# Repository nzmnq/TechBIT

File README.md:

# TechBIT — B2B IoT-система діагностики коліс, гальм та підшипників (v2.0/v2.2)

Єдиний монорепозиторій проєкту **TechBIT** на гілці `main`: багаторольова прошивка **ESP32-C3 / ESP32-S3** (CAN + ESP-NOW + Rule Engine + Black Box + LTE + BLE), апаратна плата **KiCad 10**, інженерний **React SPA** діагностичний стенд та комерційна **B2B IoT + SaaS** веб-платформа.

---

## Структура монорепозиторію

| Модуль | Призначення | Документація |
|---|---|---|
| [`website/`](website/) | B2B IoT + SaaS платформа, калькулятор ROI автопарку, Drop & Hook моніторинг, `AdminPage`, i18n (`uk`/`en`), React + Express API | [website/README.md](website/README.md) |
| [`hardware/`](hardware/) | Принципові схеми та розводка плат у `KiCad 10` (`Wheel_Sensor_Amplifier` для коліс і `S3_Master_Hub` для кабіни), 3D-моделі (`.wrl`), рендери, PDF 1:1 для ЛУТ/УФ-маски та Python-генератори | [hardware/README.md](hardware/README.md) |
| [`firmware/`](firmware/) | Прошивка `PlatformIO` TechBIT v2.0 (`c3_node`, `c3_trailer_bridge` ESP-NOW, `s3_master` Black Box + LTE + BLE, нативні тести `native_test`) | [firmware/README.md](firmware/README.md) |
| [`workbench/`](workbench/) | Інженерний стенд TechBIT v2.2 (`React Router` + `Vite` SPA + `Node.js` + `Web Serial` / Wi-Fi POST + `SSE`, порт `5050`) | [workbench/README.md](workbench/README.md) |
| [`.plans/`](.plans/) | Архітектурна специфікація об'єднання гілок у монорепозиторій | [monorepo-unification-spec.md](.plans/monorepo-unification-spec.md) |

---

## Швидкий старт за модулями

Кожен модуль є самодостатнім і запускається зі своєї підпапки:

### 1. B2B Веб-платформа ([`website/`](website/))
```bash
cd website
npm run install:all   # одноразове встановлення залежностей server/ та client/
npm run build         # збірка клієнта у website/client/dist/
npm run server        # Node.js API + роздача клієнта на http://localhost:5000
npm run client        # React dev-сервер на http://localhost:5173
```

### 2. Прошивка v2.0 ([`firmware/`](firmware/))
Відкрийте папку `firmware/` у VS Code (PlatformIO) або використовуйте CLI `pio`:
```bash
cd firmware
pio run -e c3_node            # уніфікований осьовий вузол (ESP32-C3)
pio run -e c3_trailer_bridge  # бездротовий шлюз причепа CAN -> ESP-NOW (ESP32-C3)
pio run -e s3_master          # головний блок у кабіні (ESP32-S3)
pio test -e native_test       # нативні юніт-тести DSP, CAN v2, Rules та BlackBox
```

### 3. Діагностичний SPA-стенд ([`workbench/`](workbench/))
```bash
cd workbench
npm ci                # або npm install
npm run build         # збірка SPA у workbench/dist/
npm test              # юніт- та інтеграційні тести (test_truthfulness.js)
npm start             # запуск веб-стенду на http://localhost:5050 (Chrome/Edge для Web Serial)
```

### 4. Апаратна частина та PCB ([`hardware/`](hardware/))
- Відкрийте [`hardware/kicad/Wheel_Sensor_Amplifier.kicad_pro`](hardware/kicad/Wheel_Sensor_Amplifier.kicad_pro) у **KiCad 10** (3D-моделі підключаються через відносні шляхи `${KIPRJMOD}/../3dmodels/`).
- Готові PDF 1:1 для ЛУТ, УФ-маски та монтажу розміщено у [`hardware/print/`](hardware/print/).

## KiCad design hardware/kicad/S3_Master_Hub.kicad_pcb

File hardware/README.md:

# TechBIT Hardware — Апаратна частина (колісний вузол + головний блок `ESP32-S3`)

Апаратна частина системи моніторингу вібрації, стану гальм/підшипників та температури коліс автомобіля **TechBIT** (**KiCad 10 PCB**, **3D-моделі `.wrl`**, **генератори** та **PDF 1:1 для ЛУТ і УФ-маски**).  
Нижче описані обидві плати системи:
1. **Плата колісного вузла (`Wheel_Sensor_Amplifier`, `66 × 50 мм`)** — `ESP32-C3 SuperMini` + зарядовий підсилювач `MCP6002` + `GY-SHT40` + `CAN`.
2. **Плата головного блоку в кабіні (`S3_Master_Hub`, `71 × 96 мм`)** — `ESP32-S3-DevKitC-1 N16R8` + `CAN (SN65HVD230 + 120 Ω)` + круглий `1.28" GC9A01 SPI TFT` + `microSD`.

---

## 1. Плата колісного вузла (`Wheel_Sensor_Amplifier`)

| Вигляд зверху (`F.Cu` — модулі та THT) | Вигляд знизу (`B.Cu` — SMD на міді) |
|---|---|
|  |  |

---

## Структура папки `hardware/`

```text
hardware/
├── kicad/                                      # Проєкти KiCad 10
│   ├── Wheel_Sensor_Amplifier.kicad_pro        # Проєкт колісного вузла
│   ├── Wheel_Sensor_Amplifier.kicad_sch        # Принципова схема колісного вузла
│   ├── Wheel_Sensor_Amplifier.kicad_pcb        # Розводка (66 × 50 мм, 1 шар B.Cu)
│   ├── Wheel_Sensor_Amplifier_Panel_A4.kicad_pcb  # Панель 3×5 (15 плат на аркуш A4)
│   ├── S3_Master_Hub.kicad_pro                 # Проєкт головного блоку ESP32-S3
│   ├── S3_Master_Hub.kicad_sch                 # Принципова схема та розпіновка S3 Master
│   ├── S3_Master_Hub.kicad_pcb                 # Розводка (71 × 96 мм, 1 шар B.Cu)
│   └── S3_Master_Hub_Panel_A4.kicad_pcb        # Панель 2×3 (6 плат на аркуш A4)
├── 3dmodels/                                   # Локальні 3D-моделі модулів (.wrl)
├── renders/                                    # 3D-рендери та читабельні схеми розмітки (.png)
├── print/                                      # Готові PDF 1:1 для ЛУТ, УФ-маски та монтажу
├── scripts/                                    # Python-скрипти генерації проєктів і макетів
│   ├── generate_project.py                     # Генератор колісного вузла (single + 15x panel)
│   ├── make_plate_151x102.py                   # Аркуші під текстоліт 151×102 мм (колісний вузол)
│   ├── make_a4_mixed_sheet.py                  # Змішаний аркуш A4 (5 комплектів колісного вузла)
│   ├── make_top_half_stencils.py               # УФ-маска на верхню половину A4 (колісний вузол)
│   ├── generate_s3_master.py                   # Генератор головного блоку S3_Master_Hub (single + 6x panel)
│   └── make_s3_master_prints.py                # Генератор PDF 1:1, інструкції та 3D-рендерів S3_Master_Hub
└── README.md
```

---

## Технічні характеристики плати (`Wheel Sensor Amplifier`)

- **Габарити однієї плати:** `66.0 × 50.0 мм` (оптимально для розміщення `2×2 = 4` плат на заготовці `151×102 мм` або `3×5 = 15` плат на A4).
- **Топологія:** **одностороння мідь (`B.Cu`)**, розведена без перемичок та без масивної заливки `GND` — розрахована під домашнє травлення (ЛУТ + лимонна кислота / перекис водню або хлорне залізо).
- **Гідроізоляція під заливку компаундом:** усі силові, шинні та сенсорні інтерфейси (`J1`, `J2`, `J3`) винесені кутовими роз'ємами по периметру для зручного заливання плати епоксидною смолою.
- **Паяльна маска:** розширення вікон `pad_to_mask_clearance = 0.15 мм`, суцільне заповнення контактних площадок на фотошаблонах (`B.Mask`).

---

## Склад компонентів (BOM)

### Верхня сторона (`F.Cu` — вивідні компоненти, модулі та роз'єми)
| Позиція | Компонент / Модуль | Номінал / Тип | Призначення |
|---|---|---|---|
| `U2` | Мікроконтролер | `ESP32-C3 SuperMini` | Оцифровка АЦП, I2C, CAN/TWAI (`USB-C` донизу) |
| `U1` | Операційний підсилювач | `MCP6002-I/P` (панелька `DIP-8`) | Зарядовий підсилювач ($K \approx 3$) + буфер |
| `MOD1` | DC-DC понижувач | `Mini360` (`12V → 5V`) | Живлення вузла від бортмережі авто |
| `MOD2` | CAN-трансивер | `SN65HVD230` (3.3V, 6-pin) | Інтерфейс CAN-шини (`CANH` / `CANL`) |
| `J1` | Клемник датчика вібрації | `15EDGR-5.08-02P` / `KF301-2P` (кутовий) | Вхід п'єзодатчика (`1=PIEZO+`, `2=GND`) |
| `J2` | Клемник живлення та CAN | `15EDGR-5.08-04P` / `KF301-4P` (кутовий) | Автомагістраль (`1=+12V`, `2=GND`, `3=CAN_L`, `4=CAN_H`) |
| `J3` | Роз'єм датчика температури | `JST-XH S4B-XH-A` (4-pin, кутовий 2.5 мм) | Вологостійкий датчик `GY-SHT40` (`1=3V3`, `2=GND`, `3=SDA`, `4=SCL`) |
| `R1` | Резистор THT 0.25W | `10 kΩ` | Обмеження вхідного струму ОП |
| `R2`, `R3` | Резистори THT 0.25W | `100 kΩ` (2 шт.) | Дільник опорної напруги `1.65 В` (`Vref`) |
| `R5` | Резистор THT 0.25W | `100 Ω` | Ізолюючий резистор перед ФНЧ та АЦП |
| `C5` | Конденсатор електролітичний | `10 µF` (радиальний D5/P2.5) | Фільтрація `Vref` (`+` до `VREF_1V65`) |

### Нижня сторона (`B.Cu` — SMD-монтаж на мідні доріжки)
| Позиція | Корпус | Номінал | Призначення |
|---|---|---|---|
| `D1` | `SOT-23` | `BAT54S` | Здвоєний діод Шотткі (захист входу від сплесків) |
| `C1` | `0805` | `1 nF` (NP0/C0G) | Вхідний розділовий конденсатор |
| `C2` | `0805` | `330 pF` (NP0/C0G, 50V) | Конденсатор зворотного зв'язку ($K = C_1/C_2 \approx 3$) |
| `R4` | `1206` | `4.7 MΩ` | Розрядний резистор зарядового інтегратора |
| `C3` | `1206` | `100 nF` | Блокування живлення `+3V3` біля `U1` |
| `C4` | `1206` | `100 nF` | ФНЧ антиаліасингу на вході АЦП (`R5 + C4`) |

---

## Розпіновка `ESP32-C3 SuperMini` (`U2`)

| Пін модуля | Сигнал (Net) | Підключення |
|---|---|---|
| Pin 16 (`5V`) | `+5V_BUCK` | Вихід `MOD1` (`Mini360`) |
| Pin 15 (`GND`) | `GND` | Загальна земля |
| Pin 14 (`3V3`) | `+3V3` | Живлення `U1`, `MOD2`, `J3`, `R2`, `D1` |
| Pin 11 | `ADC_SIGNAL` | Аналоговий вихід каскаду (`R5` / `C4`) |
| Pin 8 | `CAN_TX` | `MOD2` pin 3 |
| Pin 7 | `CAN_RX` | `MOD2` pin 4 |
| Pin 5 | `I2C_SCL` | `J3` pin 4 (`GY-SHT40 SCL`) |
| Pin 4 | `I2C_SDA` | `J3` pin 3 (`GY-SHT40 SDA`) |

---

## Свердління отворів

| Діаметр свердла | К-сть отворів (на 1 плату) | Елементи |
|---|---|---|
| **0.8 мм** | 40 | `R1, R2, R3, R5`, `C5`, панелька `U1` (`DIP-8`), гребінки `U2` і `MOD2` |
| **0.9 мм** | 4 | Боковий роз'єм `J3` (`JST-XH`) |
| **1.0 мм** | 4 | Контактні штирі `MOD1` (`Mini360`) |
| **1.3 мм** | 6 | Силові/шинні клемники `J1` і `J2` (`15EDGR-5.08` / `KF301`) |

---

## Файли для друку та виготовлення ([`print/`](print/))

> [!IMPORTANT]
> Друкуйте всі PDF **строго в масштабі `100%` / «Фактичний розмір»** (`Actual Size`). Вимикайте *Fit to Page* та *Borderless* (інакше драйвер розтягне плату на 2–3% і отвори не зійдуться). Перед перенесенням перевірте контрольні лінійки на аркуші (`150 мм` / `100 мм`).

| Файл | Призначення |
|---|---|
| `Plate_151x102_PagePro1350W_A4.pdf` | Оптимізовано під заготовку **`151×102 мм`** (4 плати `2×2`) та поля `≥ 4 мм`: мідь, дзеркальний верх, нижнє SMD-маркування, комбо-аркуш та УФ-маска |
| `SolderMask_UV_Film_Plate_151x102_A4.pdf` | Фотошаблони УФ паяльної маски під пластину `151×102 мм` (тонером вниз до міді + дзеркальний варіант) |
| `SolderMask_UV_Top_Half_A4.pdf` | УФ-маска, розміщена **тільки на верхній половині A4** (економія плівки: 2 плати, 4 плати `2×2`, або 2 пластини) |
| `A4_Mixed_Top_Bottom_Copper_5sets.pdf` | Змішаний аркуш A4: 5 повних комплектів (верх + мідь + низ SMD) + аркуш маркування |
| `Assembly_Guide_Readable_A4.pdf` | Читабельна карта монтажу та пайки (3 сторінки) |
| `LUT_Bottom_Copper_Max_Panel_15x_A4.pdf` / `_Single_A4.pdf` | Мідні доріжки `B.Cu` для ЛУТ (панель 15× або 1 плата) |
| `LUT_Top_Silkscreen_Transfer_Mirrored_15x_A4.pdf` / `_Single_A4.pdf` | Віддзеркалена верхня розмітка `F.SilkS` для переносу праскою |
| `LUT_Bottom_SMD_Markings_Single_A4.pdf` | Маркування SMD знизу (`B.SilkS`) |
| `SolderMask_UV_Film_15x_A4.pdf` / `_Single_A4.pdf` | Фотошаблони УФ-маски на панель 15× або 1 плату |

---

## Перегенерація та калібрування під принтер

Для повторної генерації файлів потрібні **Python 3**, **KiCad 10 (`kicad-cli`)**, **Google Chrome** (headless PDF) та `pypdf`:

```bash
# З кореня репозиторію:

# 1. Перегенерувати проєкт KiCad (одиночна плата, 15x панель, схема)
python3 scripts/generate_project.py

# 2. Перегенерувати аркуші для друку A4
python3 scripts/make_a4_mixed_sheet.py
python3 scripts/make_top_half_stencils.py

# 3. Перегенерувати аркуші під пластину 151x102 мм (з поправкою масштабу принтера у %)
python3 scripts/make_plate_151x102.py --sx 100.0 --sy 100.0
python3 scripts/make_plate_151x102.py --mask --sx 100.0 --sy 100.0
```

---

## 2. Плата головного блоку в кабіні (`S3_Master_Hub`)

| Вигляд зверху (`F.Cu` — модулі та роз'єми) | Вигляд знизу (`B.Cu` — доріжки та SMD) | Розмітка зверху (`F.SilkS`) |
|---|---|---|
|  |  |  |

### Технічні характеристики плати (`S3_Master_Hub`)

- **Габарити однієї плати:** `71.0 × 96.0 мм` (оптимально для **2 плат поруч** на заготовці `151 × 102 мм` або **2×3 = 6 плат** на аркуші A4).
- **Топологія:** **одностороння мідь (`B.Cu`)**, розведена без перемичок, переходів і заливки `GND` — під домашнє травлення (ЛУТ + УФ-маска `pad_to_mask_clearance = 0.15 мм`).
- **Сумісність з прошивкою:** 1:1 відповідає конфігурації `s3_master` (`ESP32-S3-DevKitC-1 N16R8`, 16 MB Flash + 8 MB OPI PSRAM) у [`firmware/include/board_pins.h`](../firmware/include/board_pins.h).

> [!CAUTION]
> **Важливо перед вмиканням та монтажем:**
> 1. **MP1584EN (`MOD1`):** перед впаюванням на плату подайте живлення на `IN+/IN-` окремо і викруткою виставте підстроювачем вихід рівно **`5.00 В`** (інакше заводське налаштування може спалити `ESP32-S3`). Підтримує вхід **`4.5–28 В`** (12 В авто і 24 В вантажівки) до `3 А`.
> 2. **Не подавайте `12 В` на клемник `J1` одночасно з підключеним USB-C** (якщо перемичка `IN-OUT` на `YD-ESP32-S3` запаяна або живлення йде по `5V`), щоб уникнути зворотного струму в USB-порт ПК. Для прошивки виймайте `ESP32-S3` з колодок або від'єднуйте `12 В`.
> 3. **Дисплей `1.28" GC9A01` TFT Red:** працює **строго від `3.3 В`** (`J2A.1 = +3V3`), не підключайте його до `5 В`.
> 4. **Термінатор CAN (`JP1` + `R1 120 Ω`):** якщо два колісні модулі стоять на шині, вставте перемичку на `JP1`, щоб замкнути `120 Ω` між `CAN_H` та `CAN_L` на кінці лінії з боку головного блоку.

### Склад компонентів (`S3_Master_Hub` BOM)

#### Верхня сторона (`F.Cu` — вивідні компоненти, модулі та роз'єми)
| Позиція | Компонент / Модуль | Номінал / Тип | Призначення |
|---|---|---|---|
| `U1` | Мікроконтролер | `ESP32-S3-DevKitC-1 N16R8` (2×22 PinSocket `2.54 мм`, крок рядів `25.4 мм`) | Мозок у кабіні (`Wi-Fi` вгору, подвійний `USB-C` донизу) |
| `MOD1` | DC-DC понижувач | `MP1584EN` (`D-SUN 22.1×16.8 мм`, 8 отворів, `4.5–28V → 5.0V`, 3A) | Живлення головного блоку від бортмережі |
| `MOD2` | CAN-трансивер | `SN65HVD230` (3.3V, `1×06`) | Інтерфейс CAN-шини (`GPIO4 TX` / `GPIO5 RX`) |
| `J1` | Клемник живлення та CAN | `KF301-4P` (`5.08 мм`, кутовий, входом вгору) | Бортмережа (`1=+12V`, `2=GND`, `3=CAN_L`, `4=CAN_H`) |
| `JP1` | Джампер термінатора CAN | `PinHeader 1×02` (`2.54 мм`) + перемичка | Підключає SMD-резистор `R1 120 Ω` між `CAN_H` та `CAN_L` |
| `J2A` | Роз'єм дисплея TFT (1..4) | `JST-XH S4B-XH-A` (`4-pin`, кутовий 2.5 мм, лівий край) | Червоний `1.28" GC9A01 SPI`: `3V3`, `GND`, `CS`, `RES` |
| `J2B` | Роз'єм дисплея TFT (5..8) | `JST-XH S4B-XH-A` (`4-pin`, кутовий 2.5 мм, поруч із `J2A`) | Червоний `1.28" GC9A01 SPI`: `A0/DC`, `SDA/MOSI`, `SCK`, `LED` |
| `J3` | Роз'єм MicroSD | `JST-XH S4B-XH-A` (`4-pin`, кутовий 2.5 мм, під `J2B`) | Слот `microSD` на зворотному боці дисплея (`SPI3/HSPI`) |
| `C1` | Конденсатор електролітичний | `100 µF` (радіальний D5/P2.5, ≥10V) | Буферний фільтр лінії `+5V_BUCK` (`+` на pin 1) |
| `C2` | Конденсатор електролітичний | `10 µF` (радіальний D5/P2.5, ≥6.3V) | Фільтр живлення `+3V3` (`+` на pin 1) |

#### Нижня сторона (`B.Cu` — SMD-монтаж на мідні доріжки)
| Позиція | Корпус | Номінал | Призначення |
|---|---|---|---|
| `R1` | `1206` | `120 Ω` | Термінатор шини CAN (`JP1.2 ↔ CAN_L`) |
| `C3` | `1206` | `100 nF` | ВЧ-блокування живлення `+3V3` біля роз'єму дисплея `J2A` |

### Розпіновка `ESP32-S3-DevKitC-1 N16R8` (`U1`)

| Роз'єм / Пін | Сигнал (Net) | Пін `U1` | GPIO `ESP32-S3` | Призначення |
|---|---|---|---|---|
| `J1.1` | `+12V_RAW` | — | — | Вхід `+12 В` на `MOD1` |
| `J1.2` | `GND` | `L22, R1, R21, R22` | `GND` | Загальна земля |
| `J1.3` / `J1.4` | `CAN_L` / `CAN_H` | — | — | Диференційна шина CAN (`MOD2` + `JP1/R1`) |
| `MOD2.3` / `MOD2.4` | `CAN_TX` / `CAN_RX` | `L4` / `L5` | `GPIO4` / `GPIO5` | CAN / TWAI 500 kbps |
| `J2A.1` / `J2A.2` | `+3V3` / `GND` | `L1, L2` / `GND` | `3V3` / `GND` | Живлення `1.28"` дисплея **строго 3.3 В** |
| `J2A.3` (`CS`) | `TFT_CS` | `L6` | `GPIO6` | Chip Select дисплея `GC9A01` (`SPI2/FSPI`) |
| `J2A.4` (`RES`) | `TFT_RES` | `L7` | `GPIO7` | Апаратний Reset дисплея |
| `J2B.1` (`A0/DC`) | `TFT_DC` | `L8` | `GPIO15` | Data / Command |
| `J2B.2` (`SDA`) | `TFT_MOSI` | `L9` | `GPIO16` | SPI MOSI дисплея |
| `J2B.3` (`SCK`) | `TFT_SCK` | `L10` | `GPIO17` | SPI Clock дисплея |
| `J2B.4` (`LED`) | `TFT_LED` | `L11` | `GPIO18` | PWM-підсвітка (LEDC) |
| `J3.1` (`SD_CS`) | `SD_CS` | `L15` | `GPIO9` | Chip Select `microSD` (`SPI3/HSPI`) |
| `J3.2` (`MOSI`) | `SD_MOSI` | `L16` | `GPIO10` | SPI MOSI `microSD` |
| `J3.3` (`MISO`) | `SD_MISO` | `L17` | `GPIO11` | SPI MISO `microSD` |
| `J3.4` (`SCK`) | `SD_SCK` | `L18` | `GPIO12` | SPI Clock `microSD` |

### Свердління отворів (`S3_Master_Hub`, 80 отворів на 1 плату)

| Діаметр свердла | К-сть отворів | Елементи |
|---|---|---|
| **0.9 мм** | 56 | `U1` (44), `MOD2` (6), `JP1` (2), `C1` (2), `C2` (2) |
| **0.95 мм** | 12 | `J2A` (4), `J2B` (4), `J3` (4) — бокові роз'єми `JST-XH 4P` |
| **1.0 мм** | 8 | `MOD1` (`MP1584EN`, 4 пари отворів `IN+/IN-/OUT+/OUT-`) |
| **1.3 мм** | 4 | `J1` (`KF301-4P`) |

### Файли для друку та виготовлення `S3_Master_Hub` ([`print/`](print/))

| Файл | Призначення |
|---|---|
| `S3_Master_Plate_151x102_PagePro1350W_A4.pdf` | 2 плати (`71×96 мм`) на пластину `151×102 мм`, 2 пластини на аркуші A4 (мідь `B.Cu`, дзеркальний верх `F.SilkS`, низ `B.SilkS`, комбо та UV-маска) |
| `S3_Master_SolderMask_UV_Film_Plate_151x102_A4.pdf` | UV-маска під пластину `151×102 мм` (тонером вниз до міді + дзеркальний варіант) |
| `S3_Master_SolderMask_UV_Top_Half_A4.pdf` | 2 копії UV-маски для одиничної плати `71×96 мм` на верхній половині A4 |
| `S3_Master_LUT_Single_A4.pdf` | Повний комплект 1 плати на одному аркуші A4 (`B.Cu`, дзеркальний `F.SilkS`, `B.SilkS`, `B.Mask` + лінійка `150 мм`) |
| `S3_Master_Assembly_Guide_A4.pdf` | Монтажна карта та інструкція збірки (3 сторінки: верх, дзеркальний низ, BOM, свердління і попровідні таблиці `J1/J2A/J2B/J3/JP1`) |

### Перегенерація файлів `S3_Master_Hub`

```bash
# З папки hardware/:
python3 scripts/generate_s3_master.py
python3 scripts/make_s3_master_prints.py --sx 100.0 --sy 100.0
```

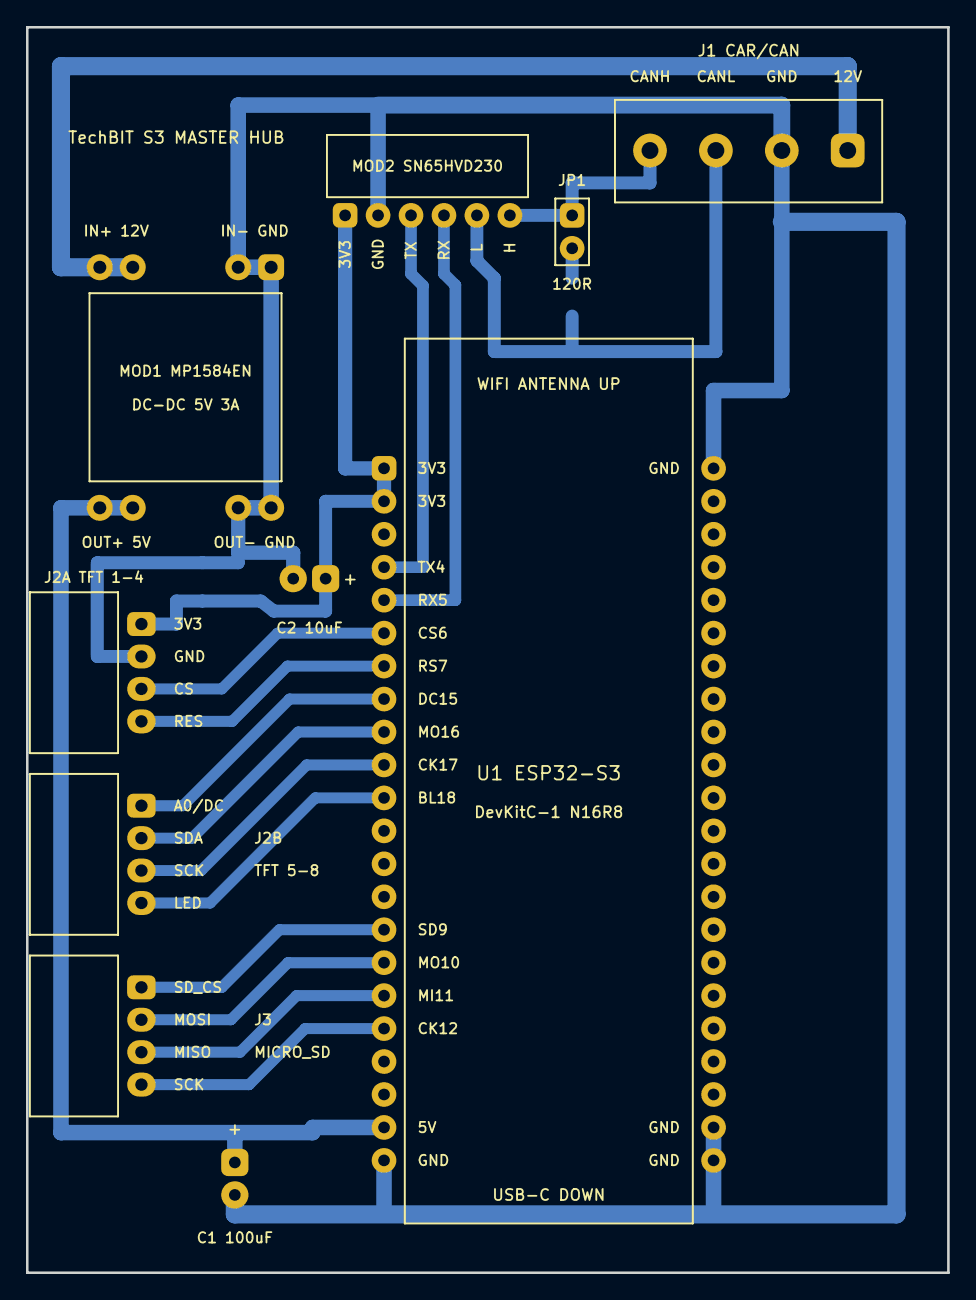
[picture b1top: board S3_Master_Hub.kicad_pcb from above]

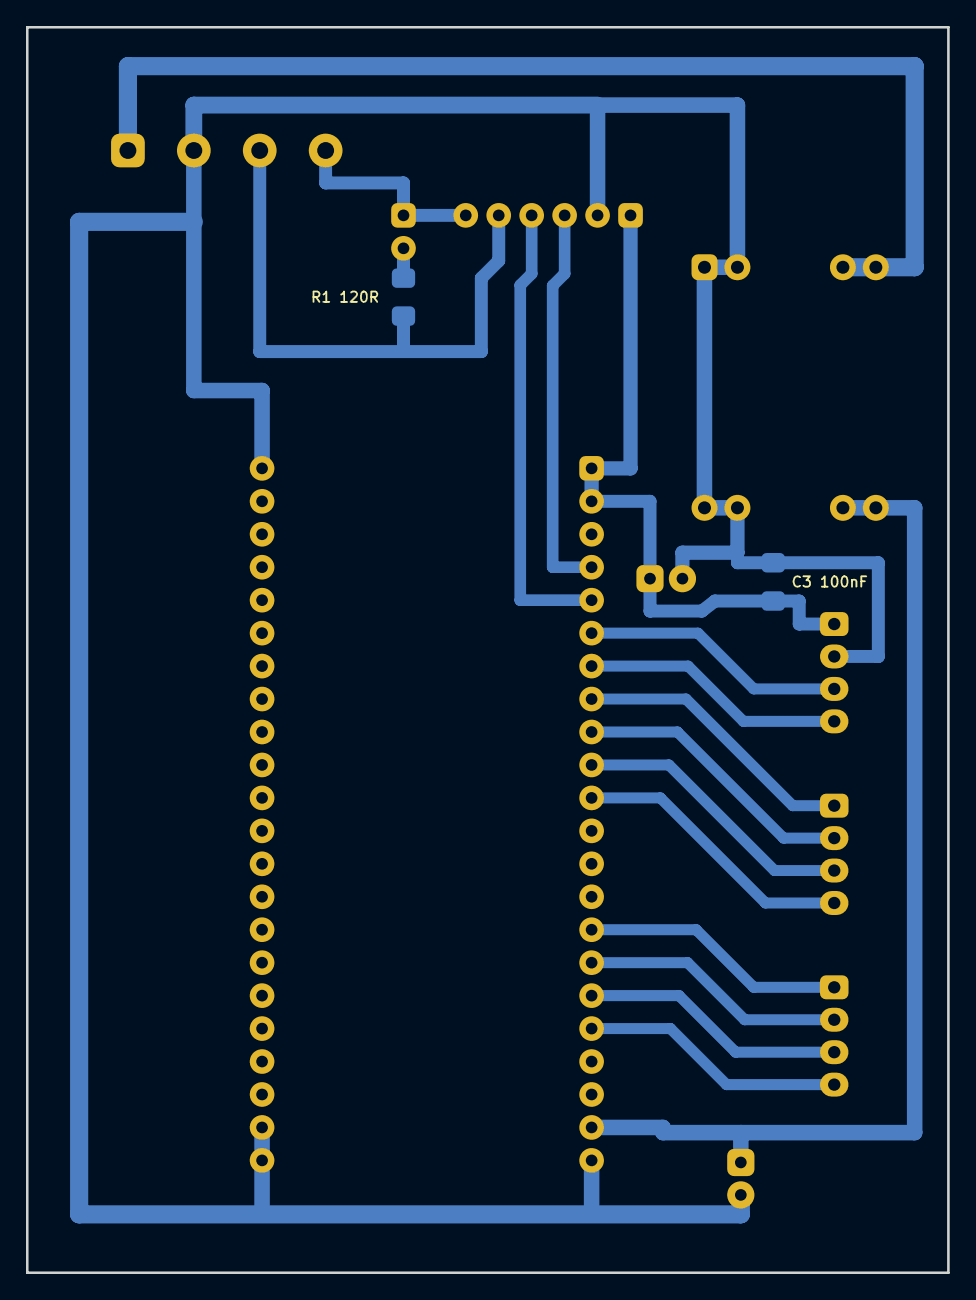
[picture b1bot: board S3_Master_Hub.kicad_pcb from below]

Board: 2 copper layers, 71.0 x 96.0 mm, 12 parts (2 on the bottom side), 19 nets.

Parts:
C1: 100uF; CP_Radial_D5.0mm_P2.50mm
C2: 10uF; CP_Radial_D5.0mm_P2.50mm
C3: 100nF; C_1206_3216Metric
J1: KF301-4P; TerminalBlock_Phoenix_MKDS-1,5-4-5.08_1x04_P5.08mm_Horizont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
J2A: TFT_1_4; JST_XH_S4B-XH-A_1x04_P2.50mm_Horizontal
J2B: TFT_5_8; JST_XH_S4B-XH-A_1x04_P2.50mm_Horizontal
J3: MICRO_SD; JST_XH_S4B-XH-A_1x04_P2.50mm_Horizontal
JP1: CAN_120R; PinHeader_1x02_P2.54mm_Vertical
MOD1: MP1584EN_5V; MP1584EN_Buck
MOD2: SN65HVD230_CAN; PinHeader_1x06_P2.54mm_Vertical
R1: 120R; R_1206_3216Metric
U1: ESP32-S3-DevKitC-1

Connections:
+3V3: C2.1, C3.2, J2A.1, MOD2.1, U1.L1, U1.L2
+5V_BUCK: C1.1, MOD1.4a, MOD1.4b, U1.L21
+12V_RAW: J1.1, MOD1.2a, MOD1.2b
CAN_H: J1.4, JP1.1, MOD2.6
CAN_L: J1.3, MOD2.5, R1.2
CAN_RX: MOD2.4, U1.L5
CAN_TERM_MID: JP1.2, R1.1
CAN_TX: MOD2.3, U1.L4
GND: C1.2, C2.2, C3.1, J1.2, J2A.2, MOD1.1a, MOD1.1b, MOD1.3a, MOD1.3b, MOD2.2, U1.L22, U1.R1, U1.R21, U1.R22
SD_CS: J3.1, U1.L15
SD_MISO: J3.3, U1.L17
SD_MOSI: J3.2, U1.L16
SD_SCK: J3.4, U1.L18
TFT_CS: J2A.3, U1.L6
TFT_DC: J2B.1, U1.L8
TFT_LED: J2B.4, U1.L11
TFT_MOSI: J2B.2, U1.L9
TFT_RES: J2A.4, U1.L7
TFT_SCK: J2B.3, U1.L10

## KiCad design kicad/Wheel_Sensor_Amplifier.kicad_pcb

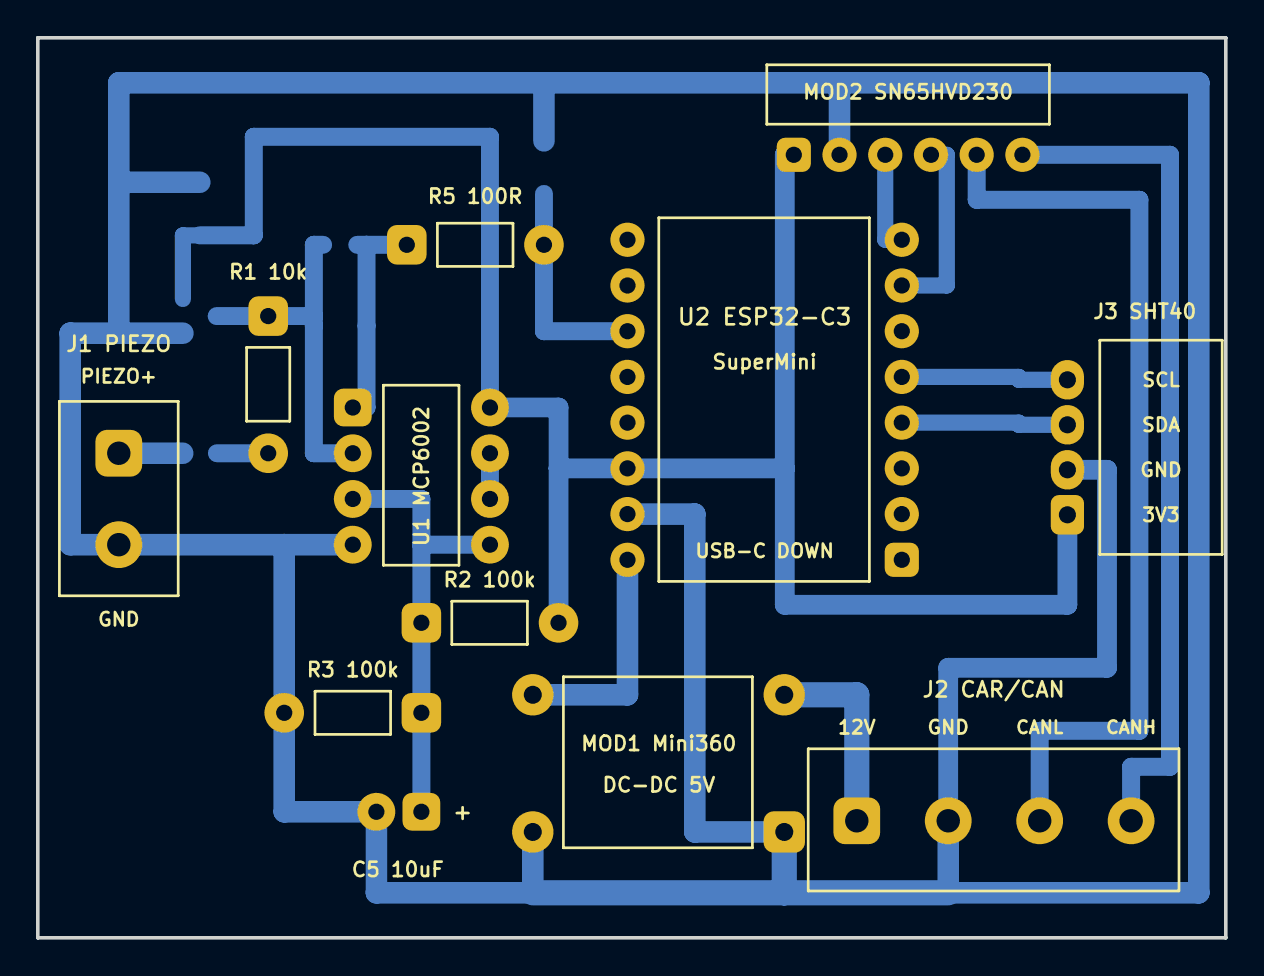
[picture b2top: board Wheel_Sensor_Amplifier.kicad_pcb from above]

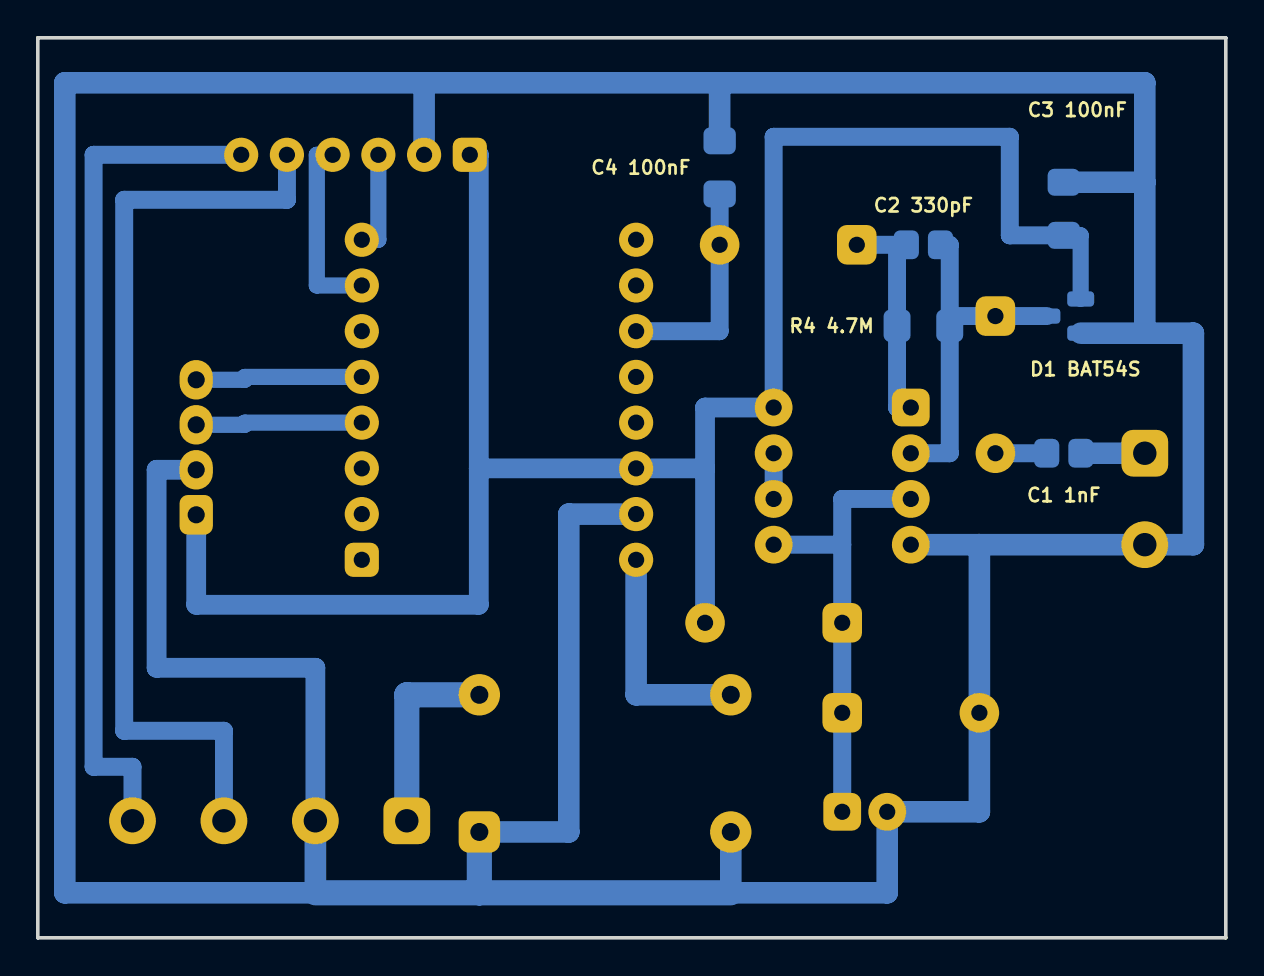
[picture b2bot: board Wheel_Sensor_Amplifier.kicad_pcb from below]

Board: 2 copper layers, 66.0 x 50.0 mm, 18 parts (6 on the bottom side), 17 nets.

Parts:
C1: 1nF; C_0805_2012Metric
C2: 330pF; C_0805_2012Metric
C3, C4: 100nF; C_1206_3216Metric
C5: 10uF; CP_Radial_D5.0mm_P2.50mm
D1: BAT54S; SOT-23
J1: PIEZO_IN; TerminalBlock_Phoenix_MKDS-1,5-2-5.08_1x02_P5.08mm_Horizont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
J2: 12V_GND_CAN; TerminalBlock_Phoenix_MKDS-1,5-4-5.08_1x04_P5.08mm_Horizont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
J3: GY-SHT40_SIDE; JST_XH_S4B-XH-A_1x04_P2.50mm_Horizontal
MOD1: Mini360_5V; Mini360_Buck
MOD2: SN65HVD230_CAN; PinHeader_1x06_P2.54mm_Vertical
R1: 10k; R_Axial_DIN0207_L6.3mm_D2.5mm_P7.62mm_Horizontal
R2, R3: 100k; R_Axial_DIN0207_L6.3mm_D2.5mm_P7.62mm_Horizontal
R4: 4.7M; R_1206_3216Metric
R5: 100R; R_Axial_DIN0207_L6.3mm_D2.5mm_P7.62mm_Horizontal
U1: MCP6002-I/P; DIP-8_W7.62mm_Socket
U2: ESP32-C3_SuperMini

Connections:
+3V3: C3.1, D1.2, J3.1, MOD2.1, R2.2, U1.8, U2.14
+5V_BUCK: MOD1.4, U2.16
+12V_RAW: J2.1, MOD1.2
ADC_SIGNAL: C4.1, R5.2, U2.11
AMP_OUT1: C2.2, R4.2, R5.1, U1.1
CAN_H: J2.4, MOD2.6
CAN_L: J2.3, MOD2.5
CAN_RX: MOD2.4, U2.7
CAN_TX: MOD2.3, U2.8
GND: C3.2, C4.2, C5.2, D1.1, J1.2, J2.2, J3.2, MOD1.1, MOD1.3, MOD2.2, R3.2, U1.4, U2.15
I2C_SCL: J3.4, U2.5
I2C_SDA: J3.3, U2.4
NODE_C1_R1: C1.2, R1.2
PIEZO_IN: C1.1, J1.1
SUM_NODE: C2.1, D1.3, R1.1, R4.1, U1.2
U1B_OUT: U1.6, U1.7
VREF_1V65: C5.1, R2.1, R3.1, U1.3, U1.5

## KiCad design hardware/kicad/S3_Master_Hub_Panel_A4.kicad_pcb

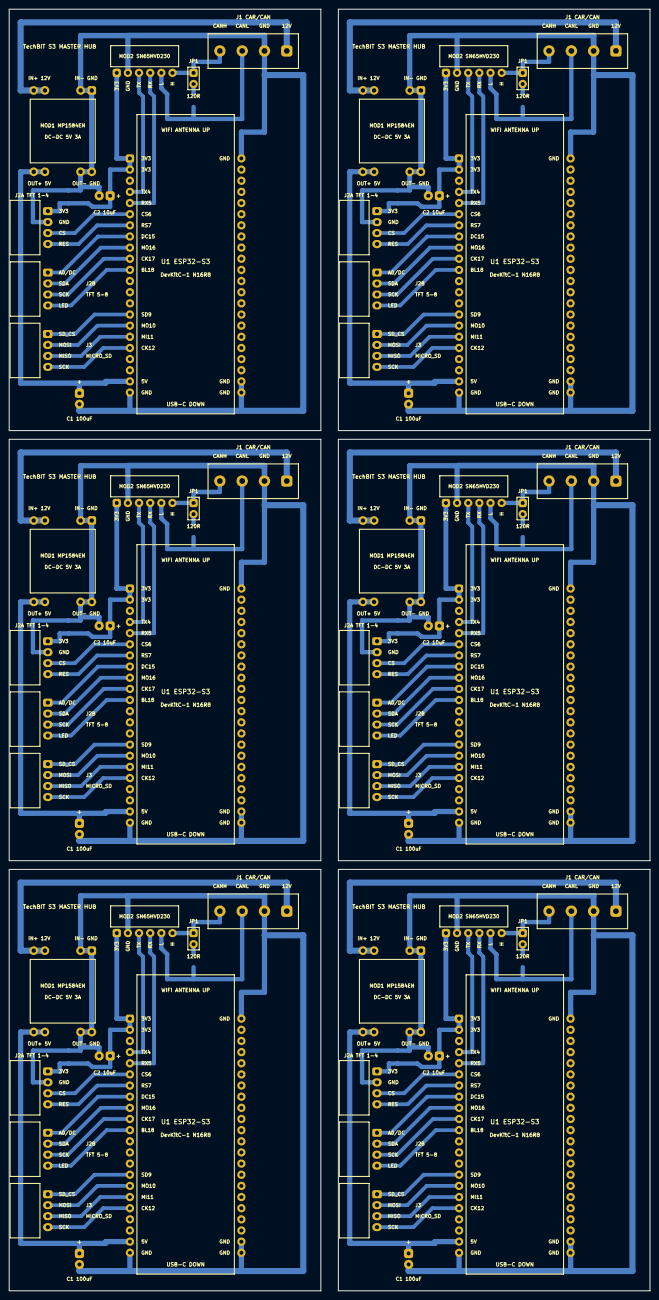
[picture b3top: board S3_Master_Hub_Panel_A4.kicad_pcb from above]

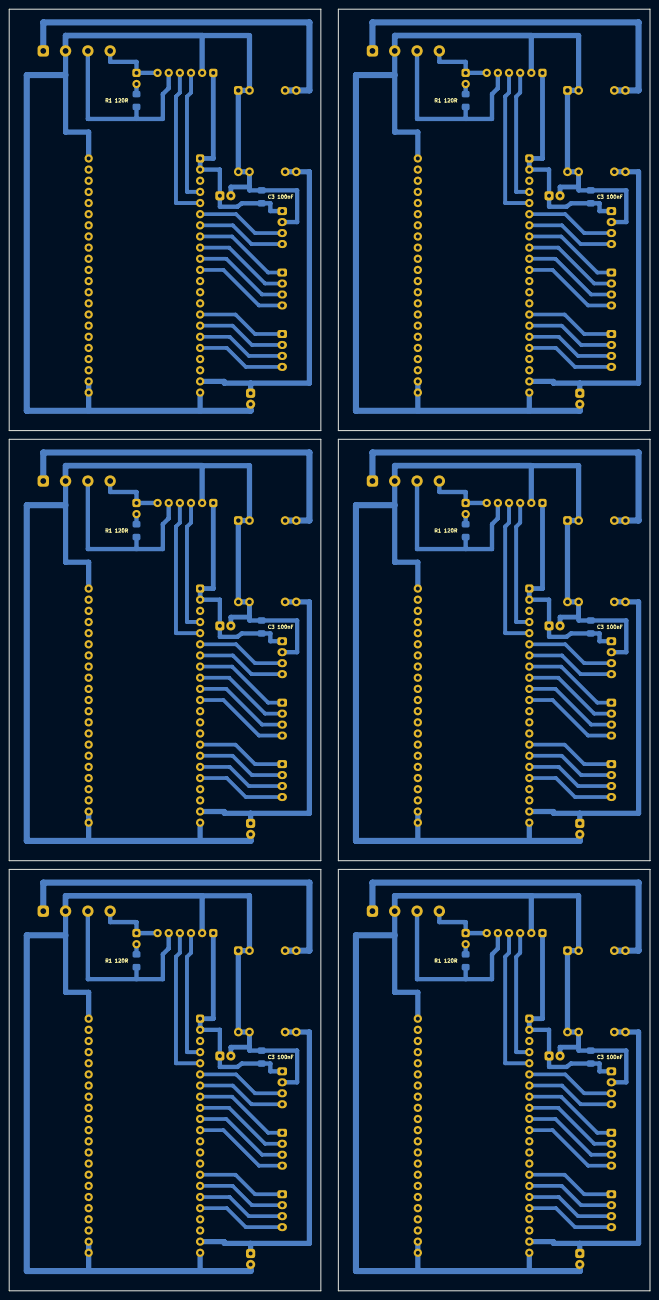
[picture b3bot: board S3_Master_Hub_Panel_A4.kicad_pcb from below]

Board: 2 copper layers, 146.0 x 292.0 mm, 72 parts (12 on the bottom side), 114 nets.

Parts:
C1_1, C1_2, C1_3, C1_4, C1_5, C1_6: 100uF; CP_Radial_D5.0mm_P2.50mm
C2_1, C2_2, C2_3, C2_4, C2_5, C2_6: 10uF; CP_Radial_D5.0mm_P2.50mm
C3_1, C3_2, C3_3, C3_4, C3_5, C3_6: 100nF; C_1206_3216Metric
J1_1, J1_2, J1_3, J1_4, J1_5, J1_6: KF301-4P; TerminalBlock_Phoenix_MKDS-1,5-4-5.08_1x04_P5.08mm_Horizont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
J2A_1, J2A_2, J2A_3, J2A_4, J2A_5, J2A_6: TFT_1_4; JST_XH_S4B-XH-A_1x04_P2.50mm_Horizontal
J2B_1, J2B_2, J2B_3, J2B_4, J2B_5, J2B_6: TFT_5_8; JST_XH_S4B-XH-A_1x04_P2.50mm_Horizontal
J3_1, J3_2, J3_3, J3_4, J3_5, J3_6: MICRO_SD; JST_XH_S4B-XH-A_1x04_P2.50mm_Horizontal
JP1_1, JP1_2, JP1_3, JP1_4, JP1_5, JP1_6: CAN_120R; PinHeader_1x02_P2.54mm_Vertical
MOD1_1, MOD1_2, MOD1_3, MOD1_4, MOD1_5, MOD1_6: MP1584EN_5V; MP1584EN_Buck
MOD2_1, MOD2_2, MOD2_3, MOD2_4, MOD2_5, MOD2_6: SN65HVD230_CAN; PinHeader_1x06_P2.54mm_Vertical
R1_1, R1_2, R1_3, R1_4, R1_5, R1_6: 120R; R_1206_3216Metric
U1_1, U1_2, U1_3, U1_4, U1_5, U1_6: ESP32-S3-DevKitC-1

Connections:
+3V3_1: C2_1.1, C3_1.2, J2A_1.1, MOD2_1.1, U1_1.L1, U1_1.L2
+3V3_2: C2_2.1, C3_2.2, J2A_2.1, MOD2_2.1, U1_2.L1, U1_2.L2
+3V3_3: C2_3.1, C3_3.2, J2A_3.1, MOD2_3.1, U1_3.L1, U1_3.L2
+3V3_4: C2_4.1, C3_4.2, J2A_4.1, MOD2_4.1, U1_4.L1, U1_4.L2
+3V3_5: C2_5.1, C3_5.2, J2A_5.1, MOD2_5.1, U1_5.L1, U1_5.L2
+3V3_6: C2_6.1, C3_6.2, J2A_6.1, MOD2_6.1, U1_6.L1, U1_6.L2
+5V_BUCK_1: C1_1.1, MOD1_1.4a, MOD1_1.4b, U1_1.L21
+5V_BUCK_2: C1_2.1, MOD1_2.4a, MOD1_2.4b, U1_2.L21
+5V_BUCK_3: C1_3.1, MOD1_3.4a, MOD1_3.4b, U1_3.L21
+5V_BUCK_4: C1_4.1, MOD1_4.4a, MOD1_4.4b, U1_4.L21
+5V_BUCK_5: C1_5.1, MOD1_5.4a, MOD1_5.4b, U1_5.L21
+5V_BUCK_6: C1_6.1, MOD1_6.4a, MOD1_6.4b, U1_6.L21
+12V_RAW_1: J1_1.1, MOD1_1.2a, MOD1_1.2b
+12V_RAW_2: J1_2.1, MOD1_2.2a, MOD1_2.2b
+12V_RAW_3: J1_3.1, MOD1_3.2a, MOD1_3.2b
+12V_RAW_4: J1_4.1, MOD1_4.2a, MOD1_4.2b
+12V_RAW_5: J1_5.1, MOD1_5.2a, MOD1_5.2b
+12V_RAW_6: J1_6.1, MOD1_6.2a, MOD1_6.2b
CAN_H_1: J1_1.4, JP1_1.1, MOD2_1.6
CAN_H_2: J1_2.4, JP1_2.1, MOD2_2.6
CAN_H_3: J1_3.4, JP1_3.1, MOD2_3.6
CAN_H_4: J1_4.4, JP1_4.1, MOD2_4.6
CAN_H_5: J1_5.4, JP1_5.1, MOD2_5.6
CAN_H_6: J1_6.4, JP1_6.1, MOD2_6.6
CAN_L_1: J1_1.3, MOD2_1.5, R1_1.2
CAN_L_2: J1_2.3, MOD2_2.5, R1_2.2
CAN_L_3: J1_3.3, MOD2_3.5, R1_3.2
CAN_L_4: J1_4.3, MOD2_4.5, R1_4.2
CAN_L_5: J1_5.3, MOD2_5.5, R1_5.2
CAN_L_6: J1_6.3, MOD2_6.5, R1_6.2
CAN_RX_1: MOD2_1.4, U1_1.L5
CAN_RX_2: MOD2_2.4, U1_2.L5
CAN_RX_3: MOD2_3.4, U1_3.L5
CAN_RX_4: MOD2_4.4, U1_4.L5
CAN_RX_5: MOD2_5.4, U1_5.L5
CAN_RX_6: MOD2_6.4, U1_6.L5
CAN_TERM_MID_1: JP1_1.2, R1_1.1
CAN_TERM_MID_2: JP1_2.2, R1_2.1
CAN_TERM_MID_3: JP1_3.2, R1_3.1
CAN_TERM_MID_4: JP1_4.2, R1_4.1
CAN_TERM_MID_5: JP1_5.2, R1_5.1
CAN_TERM_MID_6: JP1_6.2, R1_6.1
CAN_TX_1: MOD2_1.3, U1_1.L4
CAN_TX_2: MOD2_2.3, U1_2.L4
CAN_TX_3: MOD2_3.3, U1_3.L4
CAN_TX_4: MOD2_4.3, U1_4.L4
CAN_TX_5: MOD2_5.3, U1_5.L4
CAN_TX_6: MOD2_6.3, U1_6.L4
GND_1: C1_1.2, C2_1.2, C3_1.1, J1_1.2, J2A_1.2, MOD1_1.1a, MOD1_1.1b, MOD1_1.3a, MOD1_1.3b, MOD2_1.2, U1_1.L22, U1_1.R1, U1_1.R21, U1_1.R22
GND_2: C1_2.2, C2_2.2, C3_2.1, J1_2.2, J2A_2.2, MOD1_2.1a, MOD1_2.1b, MOD1_2.3a, MOD1_2.3b, MOD2_2.2, U1_2.L22, U1_2.R1, U1_2.R21, U1_2.R22
GND_3: C1_3.2, C2_3.2, C3_3.1, J1_3.2, J2A_3.2, MOD1_3.1a, MOD1_3.1b, MOD1_3.3a, MOD1_3.3b, MOD2_3.2, U1_3.L22, U1_3.R1, U1_3.R21, U1_3.R22
GND_4: C1_4.2, C2_4.2, C3_4.1, J1_4.2, J2A_4.2, MOD1_4.1a, MOD1_4.1b, MOD1_4.3a, MOD1_4.3b, MOD2_4.2, U1_4.L22, U1_4.R1, U1_4.R21, U1_4.R22
GND_5: C1_5.2, C2_5.2, C3_5.1, J1_5.2, J2A_5.2, MOD1_5.1a, MOD1_5.1b, MOD1_5.3a, MOD1_5.3b, MOD2_5.2, U1_5.L22, U1_5.R1, U1_5.R21, U1_5.R22
GND_6: C1_6.2, C2_6.2, C3_6.1, J1_6.2, J2A_6.2, MOD1_6.1a, MOD1_6.1b, MOD1_6.3a, MOD1_6.3b, MOD2_6.2, U1_6.L22, U1_6.R1, U1_6.R21, U1_6.R22
SD_CS_1: J3_1.1, U1_1.L15
SD_CS_2: J3_2.1, U1_2.L15
SD_CS_3: J3_3.1, U1_3.L15
SD_CS_4: J3_4.1, U1_4.L15
SD_CS_5: J3_5.1, U1_5.L15
SD_CS_6: J3_6.1, U1_6.L15
SD_MISO_1: J3_1.3, U1_1.L17
SD_MISO_2: J3_2.3, U1_2.L17
SD_MISO_3: J3_3.3, U1_3.L17
SD_MISO_4: J3_4.3, U1_4.L17
SD_MISO_5: J3_5.3, U1_5.L17
SD_MISO_6: J3_6.3, U1_6.L17
SD_MOSI_1: J3_1.2, U1_1.L16
SD_MOSI_2: J3_2.2, U1_2.L16
SD_MOSI_3: J3_3.2, U1_3.L16
SD_MOSI_4: J3_4.2, U1_4.L16
SD_MOSI_5: J3_5.2, U1_5.L16
SD_MOSI_6: J3_6.2, U1_6.L16
SD_SCK_1: J3_1.4, U1_1.L18
SD_SCK_2: J3_2.4, U1_2.L18
SD_SCK_3: J3_3.4, U1_3.L18
SD_SCK_4: J3_4.4, U1_4.L18
SD_SCK_5: J3_5.4, U1_5.L18
SD_SCK_6: J3_6.4, U1_6.L18
TFT_CS_1: J2A_1.3, U1_1.L6
TFT_CS_2: J2A_2.3, U1_2.L6
TFT_CS_3: J2A_3.3, U1_3.L6
TFT_CS_4: J2A_4.3, U1_4.L6
TFT_CS_5: J2A_5.3, U1_5.L6
TFT_CS_6: J2A_6.3, U1_6.L6
TFT_DC_1: J2B_1.1, U1_1.L8
TFT_DC_2: J2B_2.1, U1_2.L8
TFT_DC_3: J2B_3.1, U1_3.L8
TFT_DC_4: J2B_4.1, U1_4.L8
TFT_DC_5: J2B_5.1, U1_5.L8
TFT_DC_6: J2B_6.1, U1_6.L8
TFT_LED_1: J2B_1.4, U1_1.L11
TFT_LED_2: J2B_2.4, U1_2.L11
TFT_LED_3: J2B_3.4, U1_3.L11
TFT_LED_4: J2B_4.4, U1_4.L11
TFT_LED_5: J2B_5.4, U1_5.L11
TFT_LED_6: J2B_6.4, U1_6.L11
TFT_MOSI_1: J2B_1.2, U1_1.L9
TFT_MOSI_2: J2B_2.2, U1_2.L9
TFT_MOSI_3: J2B_3.2, U1_3.L9
TFT_MOSI_4: J2B_4.2, U1_4.L9
TFT_MOSI_5: J2B_5.2, U1_5.L9
TFT_MOSI_6: J2B_6.2, U1_6.L9
TFT_RES_1: J2A_1.4, U1_1.L7
TFT_RES_2: J2A_2.4, U1_2.L7
TFT_RES_3: J2A_3.4, U1_3.L7
TFT_RES_4: J2A_4.4, U1_4.L7
TFT_RES_5: J2A_5.4, U1_5.L7
TFT_RES_6: J2A_6.4, U1_6.L7
TFT_SCK_1: J2B_1.3, U1_1.L10
TFT_SCK_2: J2B_2.3, U1_2.L10
TFT_SCK_3: J2B_3.3, U1_3.L10
TFT_SCK_4: J2B_4.3, U1_4.L10
TFT_SCK_5: J2B_5.3, U1_5.L10
TFT_SCK_6: J2B_6.3, U1_6.L10

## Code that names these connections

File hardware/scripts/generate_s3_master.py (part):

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        "+3V3",      # L1: 3V3
        "+3V3",      # L2: 3V3
        "",          # L3: RST
        "CAN_TX",    # L4: GPIO4
        "CAN_RX",    # L5: GPIO5
        "TFT_CS",    # L6: GPIO6
        "TFT_RES",   # L7: GPIO7
        "TFT_DC",    # L8: GPIO15
        "TFT_MOSI",  # L9: GPIO16
        "TFT_SCK",   # L10: GPIO17
        "TFT_LED",   # L11: GPIO18
        "", "", "",  # L12..L14: GPIO8, GPIO3, GPIO46
        "SD_CS",     # L15: GPIO9
        "SD_MOSI",   # L16: GPIO10
        "SD_MISO",   # L17: GPIO11
        "SD_SCK",    # L18: GPIO12
        "", "",      # L19..L20: GPIO13, GPIO14
        "+5V_BUCK",  # L21: 5V
        "GND",       # L22: GND
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        "COMPLETE SINGLE-LAYER (B.Cu) TECHBIT ESP32-S3 MASTER HUB (71.0 x 96.0 mm)\\n\\n"
        "TOP SIDE (F.Cu - THT & Modules):\\n"
        "- U1: ESP32-S3-DevKitC-1 N16R8 (2x22 2.54mm PinSockets, Wi-Fi Antenna UP, Dual USB-C DOWN)\\n"
        "  Left L1..L22: L1/L2=3V3, L3=RST, L4=GPIO4(CAN_TX), L5=GPIO5(CAN_RX),\\n"
        "               L6=GPIO6(TFT_CS), L7=GPIO7(TFT_RES), L8=GPIO15(TFT_DC),\\n"
        "               L9=GPIO16(TFT_MOSI), L10=GPIO17(TFT_SCK), L11=GPIO18(TFT_LED),\\n"
        "               L15=GPIO9(SD_CS), L16=GPIO10(SD_MOSI), L17=GPIO11(SD_MISO),\\n"
        "               L18=GPIO12(SD_SCK), L21=5V, L22=GND\\n"
        "  Right R1..R22: R1=GND, R21=GND, R22=GND\\n"
        "- MOD1: MP1584EN DC-DC Buck Converter (D-SUN 22.1x16.8mm, 8 holes, 4.5-28V -> 5.0V 3A; IN+=12V, IN-=GND, OUT+=5V, OUT-=GND)\\n"
        "- MOD2: SN65HVD230 CAN Transceiver 3.3V (1=3V3, 2=GND, 3=CAN_TX, 4=CAN_RX, 5=CAN_L, 6=CAN_H)\\n"
        "- J1: KF301-4P (5.08mm) Vehicle 12V + CAN Bus (1=+12V_RAW, 2=GND, 3=CAN_L, 4=CAN_H; entry UP)\\n"
        "- JP1: 1x02 (2.54mm) CAN 120R Termination Jumper (Pin1=CAN_H, Pin2=CAN_TERM_MID -> R1 -> CAN_L)\\n"
        "- J2A: JST-XH 4P (S4B-XH-A, 2.50mm, left edge) 1.28in Red GC9A01 TFT 1..4 (1=3V3, 2=GND, 3=CS, 4=RES)\\n"
        "- J2B: JST-XH 4P (S4B-XH-A, 2.50mm, left edge) 1.28in Red GC9A01 TFT 5..8 (1=DC/A0, 2=MOSI/SDA, 3=SCK, 4=LED)\\n"
        "- J3: JST-XH 4P (S4B-XH-A, 2.50mm, left edge) 1.28in Red Module MicroSD SPI (1=SD_CS, 2=MOSI, 3=MISO, 4=SCK)\\n"
        "- C1: 100uF Radial Electrolytic (D5.0/P2.5) +5V_BUCK Bulk Filter (+ on Pin1)\\n"
        "- C2: 10uF Radial Electrolytic (D5.0/P2.5) +3V3 Filter (+ on Pin1)\\n\\n"
        "BOTTOM SIDE (B.Cu - SMD on Copper Layer):\\n"
        "- R1: 120R (1206) CAN Bus Termination Resistor (JP1 Pin2 CAN_TERM_MID <-> CAN_L)\\n"
        "- C3: 100nF (1206) +3V3 High-Frequency Decoupling Capacitor (near J2A TFT)"
    )
    sch_content = f"""(kicad_sch
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
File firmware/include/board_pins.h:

#pragma once

// ============================================================================
// TechBIT Hardware Architecture Pinout (v2.0 — Aligned with KiCad PCB & S3 Cab)
// ============================================================================

#if defined(TECHBIT_ROLE_C3_NODE)

// ---- ESP32-C3 Unified Axle Sensor Node ----
// Matched to Wheel_Sensor_Amplifier KiCad PCB (GPIO2 primary piezo + GPIO8/9 SHT40 + GPIO21/20 CAN):
// All 4 analog channels sit strictly on ADC1 (GPIO0..GPIO4).
static constexpr int PIN_VIB_LEFT_ADC    = 2;   // GPIO2 (ADC1_CH2) <- Left piezo MCP6002 output (KiCad PCB)
static constexpr int PIN_VIB_RIGHT_ADC   = 3;   // GPIO3 (ADC1_CH3) <- Right wheel piezo AFE (2nd wheel on axle)
static constexpr int PIN_TEMP_LEFT_ADC   = 0;   // GPIO0 (ADC1_CH0) <- Optional NTC L fallback
static constexpr int PIN_TEMP_RIGHT_ADC  = 4;   // GPIO4 (ADC1_CH4) <- Optional NTC R fallback

// Temperature & Humidity I2C Sensor GY-SHT40 (J3 connector on PCB, 0x44 / 0x45)
static constexpr int PIN_I2C_SDA         = 8;   // GPIO8 (shared with SuperMini blue LED!)
static constexpr int PIN_I2C_SCL         = 9;   // GPIO9
static constexpr uint8_t SHT40_I2C_ADDR  = 0x44;

// CAN Transceiver (SN65HVD230 / TJA1051 / MCP2562)
static constexpr int PIN_CAN_TX          = 21;  // GPIO21 -> CAN TXD (KiCad PCB)
static constexpr int PIN_CAN_RX          = 20;  // GPIO20 <- CAN RXD (KiCad PCB)

// Note: Do NOT blink GPIO8 when ENABLE_SHT40=1 because GPIO8 is shared with I2C SDA!
static constexpr int  PIN_STATUS_LED     = 8;
static constexpr bool STATUS_LED_ACTIVE_LOW = true;

#elif defined(TECHBIT_ROLE_C3_BRIDGE)

// ---- ESP32-C3 Trailer Wireless Bridge (Front wall of trailer) ----
static constexpr int PIN_CAN_TX          = 21;  // Trailer CAN bus TX
static constexpr int PIN_CAN_RX          = 20;  // Trailer CAN bus RX
static constexpr int PIN_BTN_PAIR        = 9;   // Press to force discovery/pairing beacon
static constexpr int PIN_STATUS_LED      = 8;
static constexpr bool STATUS_LED_ACTIVE_LOW = true;

#elif defined(TECHBIT_ROLE_S3_MASTER)

// ---- ESP32-S3-DevKitC-1 N16R8 Master & Black Box (Strictly in Cab, NO direct analog sensors!) ----
// Avoids GPIO26..37 (Octal Flash / PSRAM), GPIO19..20 (USB D-/D+), GPIO43..44 (UART0),
// GPIO38/48 (RGB LED), and strapping pins GPIO3/45/46.

// Tractor CAN bus (receives Tractor Front + Rear C3 Nodes)
static constexpr int PIN_CAN_TX          = 4;   // GPIO4 -> CAN TXD
static constexpr int PIN_CAN_RX          = 5;   // GPIO5 <- CAN RXD

// LTE Cat-1 / Cat-M1 Modem UART (SIMCom / Quectel)
static constexpr int PIN_LTE_TX          = 41;
static constexpr int PIN_LTE_RX          = 40;
static constexpr int PIN_LTE_PWRKEY      = 39;
static constexpr int PIN_LTE_RESET       = 21;

// Cabin Mini LED Indicator & Critical Buzzer
static constexpr int PIN_LED_GREEN       = 1;   // Normal system indicator
static constexpr int PIN_LED_YELLOW      = 2;   // Yellow pre-warning (> 60s)
static constexpr int PIN_LED_RED         = 42;  // Critical Red hazard
static constexpr int PIN_BUZZER          = 8;   // Optional critical buzzer (RED state)

// 1.28" Round GC9A01 240x240 SPI TFT Display (SPI2 / FSPI) -> J2A (pins 1..4) + J2B (pins 1..4)
static constexpr int PIN_TFT_CS          = 6;   // J2A.3 Display Chip Select (GPIO6 / L6)
static constexpr int PIN_TFT_RES         = 7;   // J2A.4 Display Hardware Reset (GPIO7 / L7)
static constexpr int PIN_TFT_DC          = 15;  // J2B.1 Data/Command A0 (GPIO15 / L8)
static constexpr int PIN_TFT_MOSI        = 16;  // J2B.2 SPI MOSI SDA (GPIO16 / L9)
static constexpr int PIN_TFT_SCK         = 17;  // J2B.3 SPI Clock SCK (GPIO17 / L10)
static constexpr int PIN_TFT_LED         = 18;  // J2B.4 Backlight PWM LEDC (GPIO18 / L11)

// MicroSD Card Reader on back of display (SPI3 / HSPI) -> J3 (pins 1..4)
static constexpr int PIN_SD_CS           = 9;   // J3.1 SD Card Chip Select (GPIO9 / L15)
static constexpr int PIN_SD_MOSI         = 10;  // J3.2 SD Card MOSI (GPIO10 / L16)
static constexpr int PIN_SD_MISO         = 11;  // J3.3 SD Card MISO (GPIO11 / L17)
static constexpr int PIN_SD_SCK          = 12;  // J3.4 SD Card SCK (GPIO12 / L18)

// Service Button on S3 enclosure: enables BLE Installer Service Mode for 15 minutes
static constexpr int PIN_BTN_SERVICE     = 0;   // GPIO0 (BOOT button on S3)

#endif
